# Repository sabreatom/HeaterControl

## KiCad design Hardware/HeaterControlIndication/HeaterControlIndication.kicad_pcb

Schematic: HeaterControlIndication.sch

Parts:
C1, C2: 10u; C_1206_3216Metric_Pad1.42x1.75mm_HandSolder
C3, C4, C5, C6, C7, C8: 100n; C_0603_1608Metric_Pad1.05x0.95mm_HandSolder
C9, C10: 1n; C_0603_1608Metric_Pad1.05x0.95mm_HandSolder
D1: BAR42FILM; SOT-23
F1: FX0457; Fuseholder_Cylinder-5x20mm_Bulgin_FX0457_Horizontal_Closed
J1: 282834-4; TerminalBlock_TE_282834-4_1x04_P2.54mm_Horizontal
J2: Screw_Terminal_01x03; TerminalBlock_bornier-3_P5.08mm
J3: RST_JP; PinHeader_1x02_P2.54mm_Vertical
J4: SWD; PinHeader_1x06_P2.54mm_Vertical
K1: G5LE-1; Relay_SPDT_Omron-G5LE-1
MH1, MH2, MH3, MH4: MountingHole; MountingHole_3.2mm_M3_DIN965_Pad
PS1: IRM-02-5; Converter_ACDC_MeanWell_IRM-02-xx_THT
Q1, Q2: 2N7002; SOT-23
R1: 600R; R_0805_2012Metric_Pad1.15x1.40mm_HandSolder
R2, R3, R4: 100k; R_0603_1608Metric_Pad1.05x0.95mm_HandSolder
R5: 13k7; R_0603_1608Metric_Pad1.05x0.95mm_HandSolder
R6: 26k7; R_0603_1608Metric_Pad1.05x0.95mm_HandSolder
U1: MCP1700-3302E_SOT89; SOT-89-3
U2: STM32F030K6Tx; LQFP-32_7x7mm_P0.8mm
U3: ACS712xLCTR-05B; SOIC-8_3.9x4.9mm_P1.27mm
U4: MCP601-xOT; SOT-23-5

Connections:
+3V3: C2.1, C3.2, C4.1, C5.2, C7.2, C8.2, J4.1, R3.1, U1.3 (VO), U2.1, U2.5, U2.17, U4.5 (V+)
+5V: C1.1, C6.2, D1.3, K1.5, PS1.4 (+Vout), R1.2, U1.2 (VI), U3.8
/CURR_ADC: U2.7, U4.1, U4.4 (-)
/HV_L: F1.1, J2.1
/HV_LOAD: J2.3, U3.3, U3.4
/HV_L_F: F1.2, K1.3, PS1.2 (AC/L)
/HV_N: J2.2, PS1.1 (AC/N)
/HV_ROUT: K1.1, U3.1, U3.2
/PANEL_BUT: J1.2, U2.25
/PANEL_LED: Q1.1 (G), R2.1, U2.26
/SWCLK: J4.2, U2.24
/SWDIO: J4.4, U2.23
/nRST: J3.1, J4.5, R3.2, U2.4
GND: C1.2, C2.2, C3.1, C4.2, C5.1, C6.1, C7.1, C8.1, C9.2, C10.2, J1.1, J3.2, J4.3, PS1.3 (-Vout), Q1.2 (S), Q2.2 (S), R2.2, R4.2, R6.2, U1.1 (GND), U2.16, U2.31, U2.32, U3.5, U4.2 (V-)
unnamed: C9.1, U3.6
unnamed: C10.1, R5.1, R6.1, U4.3 (+)
unnamed: D1.1, K1.2, Q2.3 (D)
unnamed: J1.3, R1.1
unnamed: J1.4, Q1.3 (D)
unnamed: Q2.1 (G), R4.1, U2.2
unnamed: R5.2, U3.7

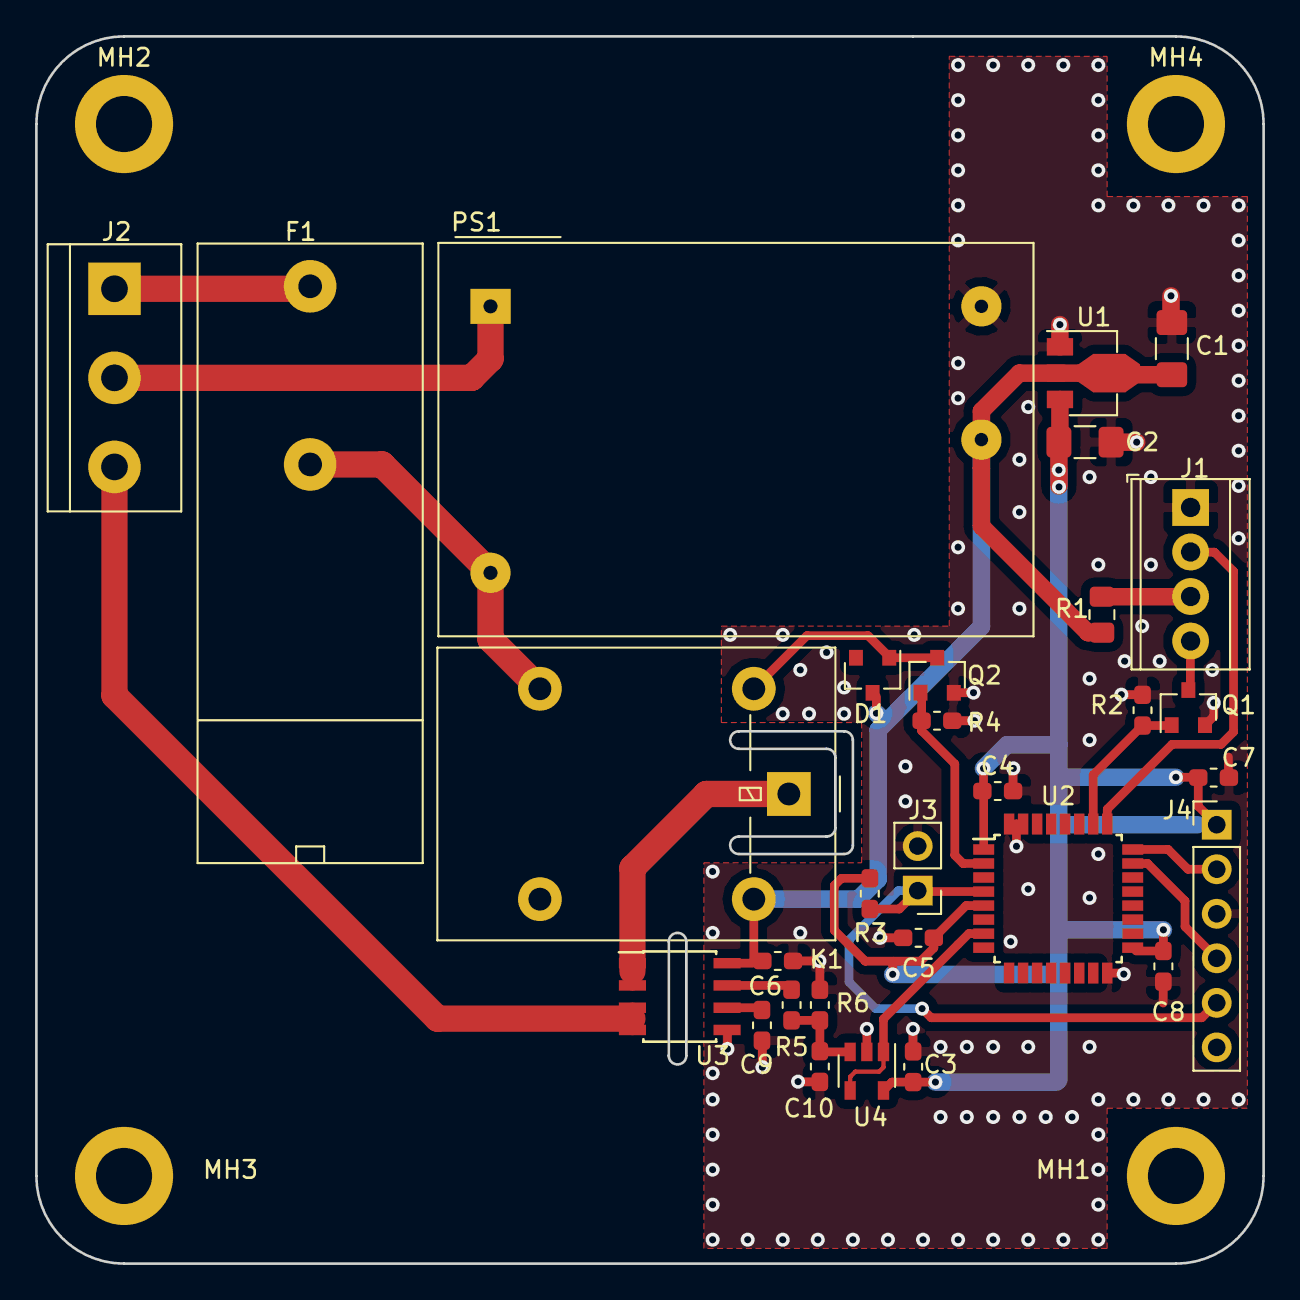
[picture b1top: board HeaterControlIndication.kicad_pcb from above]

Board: 2 copper layers, 70.0 x 70.0 mm, 34 parts (0 on the bottom side), 21 nets.

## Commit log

2019-01-28 Added PCB design and fabrication files for first version. Added initial software project.
2019-02-02 Initial software for board bringup. PCB board step 3D model.
